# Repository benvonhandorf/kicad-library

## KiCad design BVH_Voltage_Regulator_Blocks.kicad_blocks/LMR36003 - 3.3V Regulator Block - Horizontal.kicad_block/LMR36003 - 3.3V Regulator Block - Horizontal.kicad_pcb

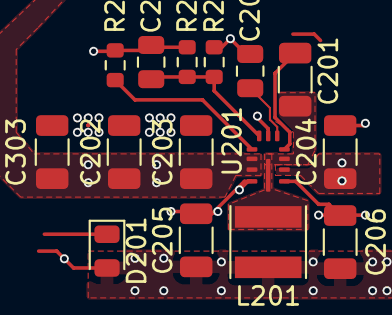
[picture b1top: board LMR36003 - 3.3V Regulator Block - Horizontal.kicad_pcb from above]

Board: 4 copper layers, 15 parts (0 on the bottom side), 8 nets.

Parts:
C201: 0.1uF; C_1206_3216Metric
C202: 4.7uF; C_1206_3216Metric
C203, C204: 220nF; C_1206_3216Metric
C205, C206: 15uF; C_1206_3216Metric
C207: 20pF; C_0805_2012Metric
C208: 1uF; C_0805_2012Metric
C303: 10uF; C_1206_3216Metric
D201: PW; LED_0805_2012Metric
L201: 10uH; L_Taiyo-Yuden_MD-4040
R201, R203: 100k; R_0603_1608Metric
R202: 43.2k; R_0603_1608Metric
U201: LMR36006; LMR36006-VQFN-HR

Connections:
+3.3V: C205.1, C206.1, C207.1, D201.2 (A), L201.2, R201.1, R203.1
+5V: C202.1, C203.1, C204.1, C303.1, U201.2 (VIN), U201.9 (EN), U201.10 (VIN)
/Power/FB: C207.2, R201.2, R202.1, U201.7 (FB)
/Power/PWR_REG_GOOD: R203.2, U201.8 (PG)
/Power/SW: C201.2, L201.1, U201.3 (SW), U201.12 (SW)
/Power/VCC: C208.1, U201.5 (VCC)
GND: C202.2, C203.2, C204.2, C205.2, C206.2, C208.2, C303.2, R202.2, U201.1 (PGND), U201.6 (AGND), U201.11 (PGND)
unnamed: C201.1, U201.4 (BOOT)

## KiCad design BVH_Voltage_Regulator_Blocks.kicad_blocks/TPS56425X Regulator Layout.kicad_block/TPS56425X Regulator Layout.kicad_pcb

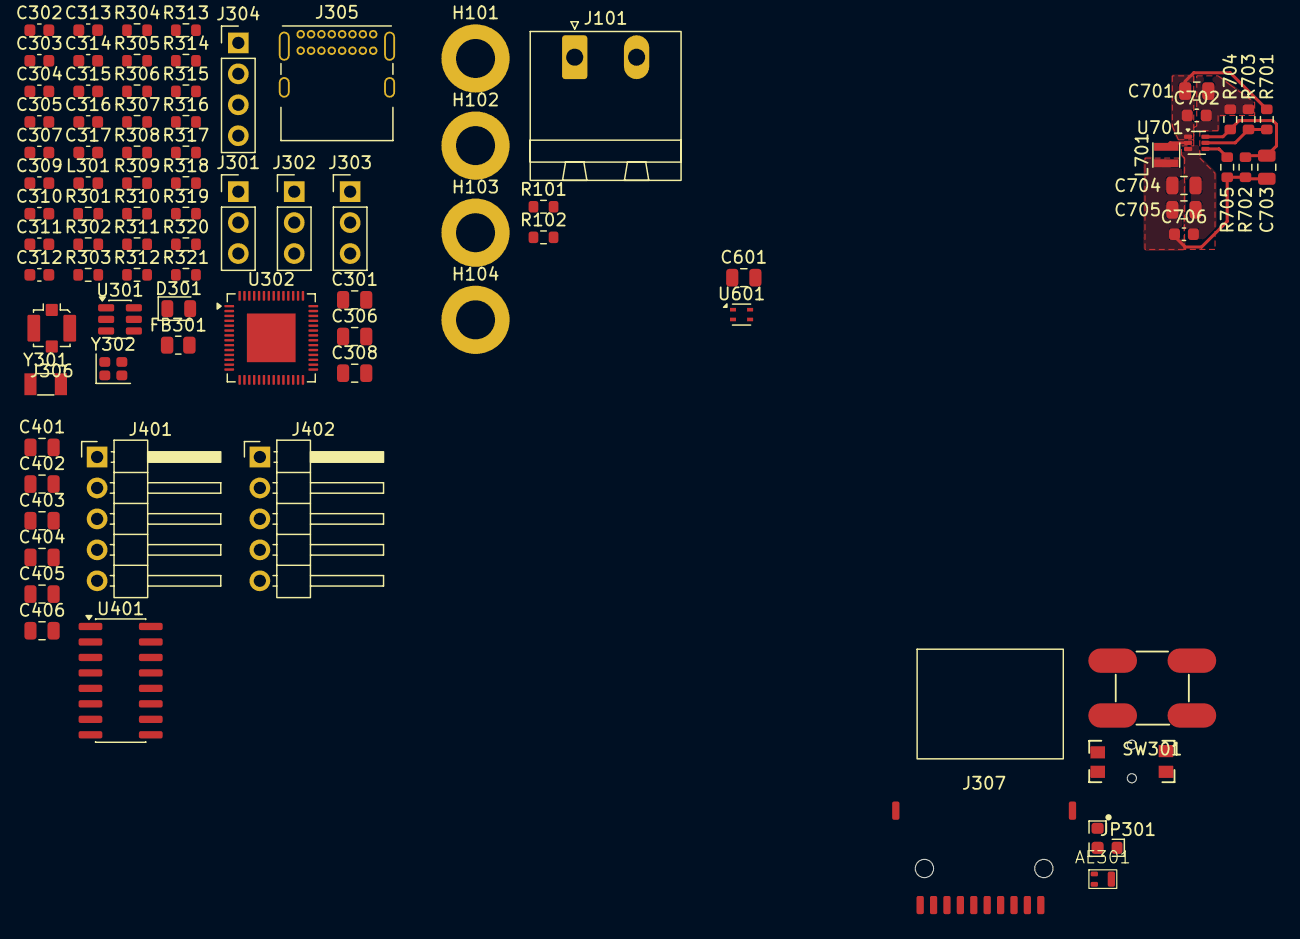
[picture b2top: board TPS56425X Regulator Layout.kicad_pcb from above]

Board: 4 copper layers, 87 parts (0 on the bottom side), 48 nets.

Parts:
AE301: ANT; ANT2012LL13R2400A
C301, C306: 10uF; C_0805_2012Metric
C302, C303, C304, C305, C307, C311, C702, C706: 0.1uF; C_0603_1608Metric
C308, C401, C402, C403, C404, C601: 1uF; C_0805_2012Metric
C309, C310: DNP; C_0603_1608Metric
C312, C313: 2.1pF; C_0603_1608Metric
C314, C315: 12.5pF; C_0603_1608Metric
C316, C317: 10pF; C_0603_1608Metric
C405, C406: DNP; C_0805_2012Metric
C701, C704, C705: 22uF; C_0805_2012Metric
C703: 10pF; C_0805_2012Metric
D301: STATUS_LED; LED_0805_2012Metric
FB301: R_0805_2012Metric
H101, H102, H103, H104: MountingHole_Pad; MountingHole_3.2mm_M3_DIN965_Pad
J101: Conn_01x02; PhoenixContact_MSTBA_2,5_2-G-5,08_1x02_P5.08mm_Horizontal
J301: UART; PinHeader_1x03_P2.54mm_Vertical
J302: EXT1; PinHeader_1x03_P2.54mm_Vertical
J303: EXT2; PinHeader_1x03_P2.54mm_Vertical
J304: I2C; PinHeader_1x04_P2.54mm_Vertical
J305: USB_C_Receptacle_USB2.0_16P; USB_C_Receptacle_GCT_USB4085
J306: Conn_Coaxial; U.FL_Molex_MCRF_73412-0110_Vertical
J307: Micro_SD_Card_Det; MicroSD_Socket_Unbranded
J401, J402: Conn_01x05; PinHeader_1x05_P2.54mm_Horizontal
JP301: RF Ant Sel; Jumper_Resistor_0603_2_Way
L301: 5.6nH; L_0603_1608Metric
L701: 3.3uH; L_Taiyo-Yuden_MD-2020
R101, R102: 2k2; R_0603_1608Metric
R301: R_Small; R_0603_1608Metric
R302, R303, R306: 100k; R_0603_1608Metric
R304, R305: 5.1k; R_0603_1608Metric
R307, R308, R311, R312, R313, R315, R316, R317, R318, R319: 50k; R_0603_1608Metric
R309, R310, R320, R321: 0; R_0603_1608Metric
R314: 33R; R_0603_1608Metric
R701: 51.1 k; R_0603_1608Metric
R702: 45.3 k; R_0603_1608Metric
R703: 30 k; R_0603_1608Metric
R704, R705: 10 k; R_0603_1608Metric
SW301: BOOT; TacButton_SMD_5mm_5mm
SW302: RST; Tac_SMD_6.4mm_Side_SPST_NO
U301: SOT-23-6
U302: ESP32-S3; QFN-56-1EP_7x7mm_P0.4mm_EP4x4mm
U401: SOIC-16_3.9x9.9mm_P1.27mm
U601: SHT4x; Sensirion_DFN-4_1.5x1.5mm_P0.8mm_SHT4x_NoCentralPad
U701: TPS564257DRLR; SOT-563
Y301: 32kHz RTC Crystal; Crystal_SMD_3215-2Pin_3.2x1.5mm
Y302: 40 MHz; Crystal_SMD_2016-4Pin_2.0x1.6mm

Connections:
+3.3V: C301.1, C302.1, C303.1, C304.1, C306.1, C307.1, C311.2, C401.1, C601.1, C703.1, C704.1, C705.1, C706.1, FB301.2, J304.2, L701.2, R101.1, R102.1, R302.2, R303.2, R306.2, R307.2, R308.1, R311.2, R312.2, R313.2, R314.1, R315.2, R316.1, R317.2, R318.2, R319.2, R702.1, R705.1, U301.5 (VCC), U302.2 (VDD3P3), U302.3 (VDD3P3), U302.20 (VDD3P3_RTC), U302.46 (VDD3P3_CPU), U401.15 (Vdd), U601.3 (VDD)
/Load Cell Sensor/E_p: C402.1, C403.1, J401.5, J402.5, U401.1 (REFP), U401.16 (VddA)
/Load Cell Sensor/S1_N: C406.1, J401.3, U401.2 (VIN1N)
/Load Cell Sensor/S1_P: C406.2, J401.2, U401.3 (VIN1P)
/Load Cell Sensor/S2_N: C405.1, J402.3, U401.4 (VIN2N)
/Load Cell Sensor/S2_P: C405.2, J402.2, U401.5 (VIN2P)
/Load Cell Sensor/SCK: J304.4, R101.2, U302.24 (GPIO18), U401.13 (SCK), U601.2 (SCL)
/Load Cell Sensor/SDA: J304.3, R102.2, U302.23 (GPIO17), U401.14 (SDA), U601.1 (SDA)
/Microprocessor/CHIP_EN: C308.1, R306.1, SW302.2 (B), U302.4 (CHIP_PU)
/Microprocessor/GPIO3_STRAP_PD: R302.1, U302.8 (GPIO3)
/Microprocessor/RF: C312.1, L301.1, U302.1 (LNA_IN)
/Microprocessor/RF_ANT: C313.1, JP301.2 (C), L301.2
/Microprocessor/SD_CMD: J307.3 (CMD), R316.2, U302.41 (GPIO36)
/Microprocessor/SD_CS: J307.2 (DAT3/CD), R307.1
/Microprocessor/SD_DAT0: J307.7 (DAT0), R315.1, U302.39 (GPIO34)
/Microprocessor/SD_DAT1: J307.8 (DAT1), R317.1, U302.38 (GPIO33)
/Microprocessor/SD_DAT2: J307.1 (DAT2), R308.2, R318.1, U302.43 (GPIO38)
/Microprocessor/SD_DAT3: R319.1, U302.42 (GPIO37)
/Microprocessor/SD_DET: J307.10 (DET_A), U302.44 (GPIO39/MTCK)
/Microprocessor/SD_SCK: J307.5 (CLK), U302.40 (GPIO35)
/Microprocessor/STATUS_LED: R301.2, U302.51 (GPIO45)
/Microprocessor/UART_RX: J301.2, U302.50 (GPIO44/U0RXD)
/Microprocessor/UART_TX: J301.3, U302.49 (GPIO43/U0TXD)
/Microprocessor/USB_N: C309.1, J305.A7 (D-), J305.B7 (D-), R309.1, U301.1 (IO1)
/Microprocessor/USB_P: C310.1, J305.A6 (D+), J305.B6 (D+), R310.1, U301.4 (IO2)
/Microprocessor/USB_uC_N: R309.2, U302.25 (GPIO19/USB_D-)
/Microprocessor/USB_uC_P: R310.2, U302.26 (GPIO20/USB_D+)
/Microprocessor/VDD33A: C305.1, FB301.1, U302.55 (VDDA), U302.56 (VDDA)
/Microprocessor/V_usb: J305.A4 (VBUS), J305.A9 (VBUS), J305.B4 (VBUS), J305.B9 (VBUS)
/Microprocessor/XTAL_32K_N: C315.1, U302.22 (GPIO16/XTAL_32K_N*), Y301.2
/Microprocessor/XTAL_32K_P: R320.1, U302.21 (GPIO15/XTAL_32K_P*)
/Microprocessor/XTAL_N: C317.1, U302.53 (XTAL_N), Y302.3
/Microprocessor/XTAL_P: R321.1, U302.54 (XTAL_P)
/TPS56425X Regulator/PWR_GD: R705.2, U701.4 (PG)
/TPS56425X Regulator/Vin: C701.1, C702.1, J101.2, J302.2, J303.2, R701.1, U701.1 (Vin)
GND: AE301.2 (GND), C301.2, C302.2, C303.2, C304.2, C305.2, C306.2, C307.2, C308.2, C309.2, C310.2, C311.1, C312.2, C313.2, C314.2, C315.2, C316.2, C317.2, C401.2, C402.2, C403.2, C404.1, C601.2, C701.2, C702.2, C704.2, C705.2, C706.2, D301.1 (K), H101.1 (1_1), H102.1 (1_1), H103.1 (1_1), H104.1 (1_1), J101.1, J301.1, J302.1, J303.1, J304.1, J305.A1 (GND), J305.A12 (GND), J305.B1 (GND), J305.B12 (GND), J306.2 (Ext), J307.6 (VSS), J307.9 (DET_B), J401.1, J401.4, J402.1, J402.4, R304.1, R305.1, R703.2, R704.2, SW301.2 (B), SW302.1 (A), U301.2 (GND), U401.7 (REFN), U401.8 (AGND), U401.9 (GND), U601.4 (VSS), U701.3 (GND), Y302.2, Y302.4
unnamed: AE301.1 (A), JP301.1 (A)
unnamed: C314.1, R320.2, Y301.1
unnamed: C316.1, R321.2, Y302.1
unnamed: D301.2 (A), R301.1
unnamed: J305.A5 (CC1), R304.2
unnamed: J305.B5 (CC2), R305.2
unnamed: J306.1 (In), JP301.3 (B)
unnamed: J307.4 (VDD), R314.2
unnamed: C404.2, U401.6 (VBG)
unnamed: R701.2, R703.1, U701.5 (EN)
unnamed: C703.2, R702.2, R704.1, U701.6 (FB)
unnamed: L701.1, U701.2 (SW)

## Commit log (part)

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2017-11-11 Starting on swtich footprints
2017-11-11 Reorganizing and new footprints
2017-11-16 More voltage regulators
2017-11-27 Fixes for oshpark
2017-12-11 Drill hole size fixes from prototype
2018-03-13 xbox joystick, fpc connector
2018-03-23 Joystick iteration 2
2019-04-17 Added NRF52840 E73 module
2019-05-08 Switches and buttons and connectors
2019-05-15 Created handsoldered E73 footprint
2019-12-01 Misc connectors and TRRS jack
2020-05-16 PSP Joystick work
2020-05-17 Pot and logo footprints
2020-05-21 Add LF indicators to relevant E73 pins
2020-05-23 SMD side tac switch
2020-05-29 XF3M Connectors
2020-05-31 Library cleanup
2020-06-02 AB4EN Orbitron logo
2020-06-23 Add PAW3204 symbol
2021-03-07 Before nightlies
2021-04-05 SK6812E Mini and Keyswitches:
2021-04-06 Fix for Kailh switch pin placement
2021-04-28 Fix for encoder footprint
2022-06-11 Rescuing circular placement plugins
2022-10-30 SOICbite work
2022-12-21 Library changes
2023-07-20 NAU7802 and others
2023-10-24 TVS Diode
2024-10-17 Misc LEDs, Switches, etc
2024-11-16 Touch pad WIP
2024-11-16 Touch pad scripts
2024-11-18 WIP Touchpad
2024-11-30 PCB Antenna WIP
2024-11-30 Resistor jumper fix
2024-12-06 Footprint Advent 1
2024-12-07 Footprintvent Catchup
2024-12-07 Footprintvent
2024-12-09 EVQWJN Updates
2025-03-07 LED Footprints
2025-03-16 Vertical LED footprint
2025-03-16 Fix footprint, add jobset
2025-03-16 Add drill data to export
2025-03-17 Fix for side tac switch footprint
2025-04-03 1204 side firing pin order
2025-04-09 Combo common numbering changes
2025-05-20 Added display connectors
2025-05-24 Update display connectors
2025-05-24 Added CF42 footprints for 40 12 and 06
2025-06-05 Added NAU8822 Footprint
2025-06-06 Symbol Updated
2025-06-06 Electret microphone footprint
2025-06-08 Combo button LED
2025-06-09 Update pins and footprints
2025-06-10 FrictionRetention PinHeader Library
2025-06-10 PinPaste USB footprint and routable mousebite
2025-06-11 Anchored pinheaders
2025-06-12 Added analog pin annotation
2025-06-12 Footprint improvements
2025-06-12 Antnna footprint silkscreen and footprint
